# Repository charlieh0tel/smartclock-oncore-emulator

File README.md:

# smartclock-oncore-emulator

*Two VP Oncores (top left) and two boards, each on a test jig.*

A drop-in replacement for the Motorola VP Oncore GPS engine in HP and
Symmetricom SmartClocks: the Z3801A, Z3805A, 58503A and their kin.  A
u-blox LEA-M8T timing module and an STM32C091 speak the Oncore
protocol to the instrument and pass the module's 1 PPS straight
through.

It is not a full Oncore replacement.  It implements exactly the Oncore
messages that every known HP SmartClock firmware sends, each in full,
and no others (`docs/oncore-messages.md`).

## Status

- Firmware [fw-v1.0.0](https://github.com/charlieh0tel/smartclock-oncore-emulator/releases/tag/fw-v1.0.0):
  an image for each receiver model, with SHA256SUMS.
- Every SmartClock image locks in emulation, against the board on
  its test jig
  ([coverage](https://charlieh0tel.github.io/smartclock-oncore-emulator/coverage.html),
  `docs/testing.md`).
- In a 58503A, 16 hours locked with no alarm, its 1 PPS checked
  against a CNS Clock II (`docs/emu-board-bring-up.md`,
  [charts](https://claude.ai/artifact/BKLhqv7PK5DPNSiXxLh1z2)).
- Like a VP Oncore, it has a fixed bias against UTC, tens of
  nanoseconds, which each instrument can trim with
  `:DIAGnostic:TOFFset` (`docs/emu-board-bring-up.md`).
- Board rev 1.0.0.

Boards are not for sale; `hardware/` and `production/` have what is
needed to have one made.

## Layout

| Path | What |
|---|---|
| `hardware/` | KiCad designs: the board and its test jig |
| `production/` | each board's fabrication files (Gerbers, BOM, placement, source) |
| `firmware/` | the Rust firmware and its host tools (`firmware/README.md`) |
| `bench/` | bench tools: flashing, 1 PPS comparison (`bench/README.md`) |
| `docs/` | the messages, the connector, bring-up and test results |
| `PLAN.md` | the design and its reasons |
| `third_party/` | vendor documents (`third_party/NOTICE`) |

## Sources

The protocol is the VP Oncore Command Reference
(`third_party/motorola/VPCommands.pdf`), implemented by smartclock-gps.
How the SmartClock firmware uses it is in
[smartclock](https://github.com/charlieh0tel/smartclock)'s
`docs/firmware/gps.md`.

## License

- Hardware: CERN-OHL-S-2.0 (`hardware/LICENSE`).  Footprints adapted
  from KiCad's library stay CC-BY-SA-4.0; each 3D model keeps its
  source's terms (the `.3dshapes` READMEs); `hardware/ee_tooling` is
  MIT OR Apache-2.0.
- Firmware and documentation: GPL-3.0-only (`LICENSE`).
- `third_party/`: its owners' (`third_party/NOTICE`).

## Contributing

Once per clone: `git submodule update --init` and `make hooks`.
`AGENTS.md` has the rules.

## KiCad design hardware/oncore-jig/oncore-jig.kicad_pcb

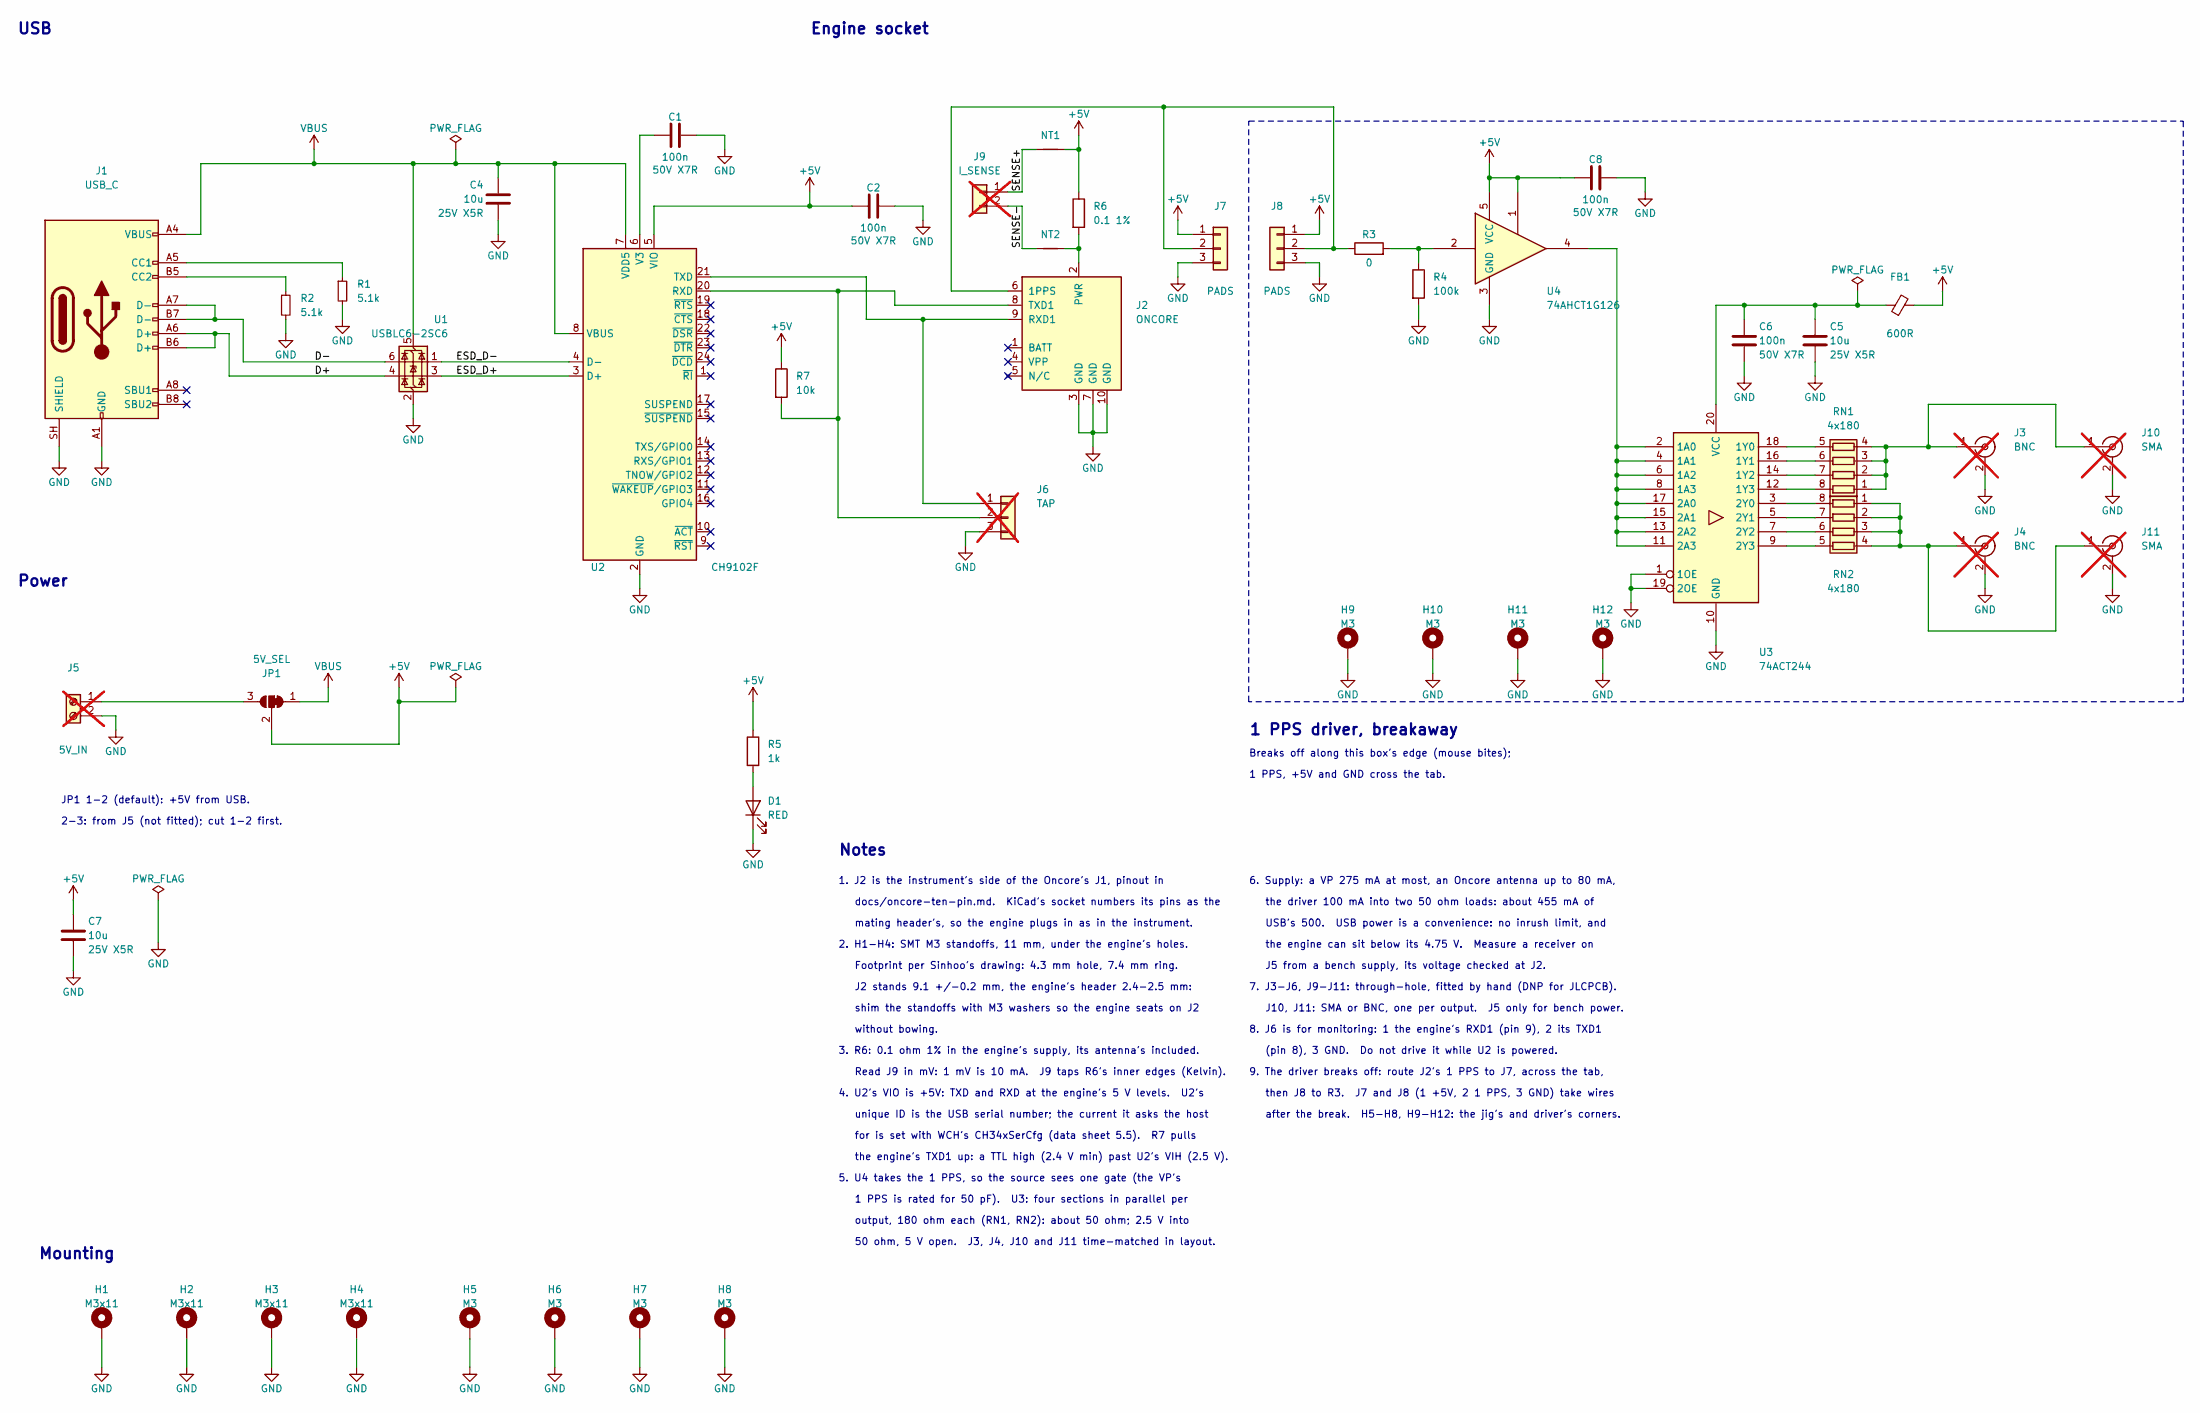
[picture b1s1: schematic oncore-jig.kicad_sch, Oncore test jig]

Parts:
C1, C2, C6, C8: 100n; C_0603_1608Metric; Rating 50V X7R; MPN CC0603KRX7R9BB104; LCSC C14663
C4, C5, C7: 10u; C_0805_2012Metric; Rating 25V X5R; MPN CL21A106KAYNNNE; LCSC C15850
D1: RED; LED_0603_1608Metric; MPN KT-0603R; LCSC C2286
FB1: 600R; L_0603_1608Metric; MPN GZ1608D601TF; LCSC C1002
H1, H2, H3, H4: M3x11; Sinhoo_SMTSO30110CTJ-B; MPN SMTSO30110CTJ-B; LCSC C2916372
H5, H6, H7, H8, H9, H10, H11, H12: M3; MountingHole_3.2mm_Pad5.0_Via
J1: USB_C; USB_C_Receptacle_HRO_TYPE-C-31-M-12; MPN TYPE-C-31-M-12; LCSC C165948
J2: ONCORE; PinSocket_2x05_P2.54mm_Vertical_SMD_BOOMELE; MPN 2.54-2*5P; LCSC C261072
J3, J4: BNC; BNC_TEConnectivity_1478035_Horizontal; MPN 1-1478035-0; not fitted
J5: 5V_IN; TerminalBlock_Phoenix_MPT-0,5-2-2.54_1x02_P2.54mm_Horizontal; MPN 1725656; not fitted
J6: TAP; PinHeader_1x03_P2.54mm_Vertical; MPN PZ254V-11-03P; LCSC C2937625; not fitted
J7, J8: PADS; PinHeader_1x03_P2.54mm_Vertical
J9: I_SENSE; PinHeader_1x02_P2.54mm_Vertical; MPN PZ254V-11-02P; LCSC C492401; not fitted
J10, J11: SMA; SMA_BAT_Wireless_BWSMA-KWE-Z001; MPN BWSMA-KWE-Z001; LCSC C496551; not fitted
JP1: 5V_SEL; SolderJumper-3_P1.3mm_Bridged12_RoundedPad1.0x1.5mm_NumberL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
NT1, NT2: NetTie_2; NetTie-2_SMD_Pad0.5mm
R1, R2: 5.1k; R_0603_1608Metric; MPN 0603WAF5101T5E; LCSC C23186
R3: 0; R_0603_1608Metric; MPN 0603WAF0000T5E; LCSC C21189
R4: 100k; R_0603_1608Metric; MPN 0603WAF1003T5E; LCSC C25803
R5: 1k; R_0603_1608Metric; MPN 0603WAF1001T5E; LCSC C21190
R6: 0.1 1%; R_0805_2012Metric; MPN FBF05FTPR100; LCSC C2929805
R7: 10k; R_0603_1608Metric; MPN 0603WAF1002T5E; LCSC C25804
RN1, RN2: 4x180; R_Array_Convex_4x0603; MPN 4D03WGJ0181T5E; LCSC C11998
U1: USBLC6-2SC6; SOT-23-6; MPN USBLC6-2SC6; LCSC C7519
U2: CH9102F; QFN-24-1EP_4x4mm_P0.5mm_EP2.6x2.6mm_CenterVia; MPN CH9102F; LCSC C2858418
U3: 74ACT244; TSSOP-20_4.4x6.5mm_P0.65mm; MPN SN74ACT244PWR; LCSC C6930
U4: 74AHCT1G126; SOT-23-5; MPN SN74AHCT1G126DBVR; LCSC C163712

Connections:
+5V: C2.1, C7.1, C8.1, FB1.2, J7.1, J8.1, JP1.2 (C), NT1.2, R5.1, R6.1, R7.1, U2.5 (VIO), U4.1, U4.5 (VCC)
/D+: J1.A6 (D+), J1.B6 (D+), U1.4 (I/O2)
/D-: J1.A7 (D-), J1.B7 (D-), U1.6 (I/O1)
/ESD_D+: U1.3 (I/O2), U2.3 (D+)
/ESD_D-: U1.1 (I/O1), U2.4 (D-)
/SENSE+: J9.1, NT1.1
/SENSE-: J9.2, NT2.1
GND: C1.2, C2.2, C4.2, C5.2, C6.2, C7.2, C8.2, D1.1 (K), H1.1, H2.1, H3.1, H4.1, H5.1, H6.1, H7.1, H8.1, H9.1, H10.1, H11.1, H12.1, J1.A1 (GND), J1.A12 (GND), J1.B1 (GND), J1.B12 (GND), J1.SH (SHIELD), J2.3 (GND), J2.7 (GND), J2.10 (GND), J3.2 (Ext), J4.2 (Ext), J5.2, J6.3, J7.3, J8.3, J10.2 (Ext), J11.2 (Ext), R1.2, R2.2, R4.2, U1.2 (GND), U2.2 (GND), U2.25 (GND), U3.1 (1OE), U3.10 (GND), U3.19 (2OE), U4.3 (GND)
unnamed: D1.2 (A), R5.2
unnamed: J1.A5 (CC1), R1.1
unnamed: J1.B5 (CC2), R2.1
unnamed: J2.6 (1PPS), J7.2, J8.2, R3.1
unnamed: J2.2 (PWR), NT2.2, R6.2
unnamed: J2.9 (RXD1), J6.1, U2.21 (TXD)
unnamed: J2.8 (TXD1), J6.2, R7.2, U2.20 (RXD)
unnamed: J5.1, JP1.3 (B)
unnamed: J3.1 (In), J10.1 (In), RN1.1 (R1.1), RN1.2 (R2.1), RN1.3 (R3.1), RN1.4 (R4.1)
unnamed: J4.1 (In), J11.1 (In), RN2.1 (R1.1), RN2.2 (R2.1), RN2.3 (R3.1), RN2.4 (R4.1)
unnamed: R3.2, R4.1, U4.2
unnamed: RN1.8 (R1.2), U3.12 (1Y3)
unnamed: RN1.7 (R2.2), U3.14 (1Y2)
unnamed: RN1.6 (R3.2), U3.16 (1Y1)
unnamed: RN1.5 (R4.2), U3.18 (1Y0)
unnamed: RN2.8 (R1.2), U3.3 (2Y0)
unnamed: RN2.7 (R2.2), U3.5 (2Y1)
unnamed: RN2.6 (R3.2), U3.7 (2Y2)
unnamed: RN2.5 (R4.2), U3.9 (2Y3)
unnamed: C1.1, U2.6 (V3)
unnamed: U3.2 (1A0), U3.4 (1A1), U3.6 (1A2), U3.8 (1A3), U3.11 (2A3), U3.13 (2A2), U3.15 (2A1), U3.17 (2A0), U4.4
unnamed: C5.1, C6.1, FB1.1, U3.20 (VCC)
VBUS: C4.1, J1.A4 (VBUS), J1.A9 (VBUS), J1.B4 (VBUS), J1.B9 (VBUS), JP1.1 (A), U1.5 (VBUS), U2.7 (VDD5), U2.8 (VBUS)

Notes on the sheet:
the driver 100 mA into two 50 ohm loads: about 455 mA of
mating header's, so the engine plugs in as in the instrument.
USB's 500. USB power is a convenience: no inrush limit, and
3. R6: 0.1 ohm 1% in the engine's supply, its antenna's included.
JP1 1-2 (default): +5V from USB.
Mounting
for is set with WCH's CH34xSerCfg (data sheet 5.5). R7 pulls
USB
Footprint per Sinhoo's drawing: 4.3 mm hole, 7.4 mm ring.
shim the standoffs with M3 washers so the engine seats on J2
1 PPS is rated for 50 pF). U3: four sections in parallel per
50 ohm, 5 V open. J3, J4, J10 and J11 time-matched in layout.
9. The driver breaks off: route J2's 1 PPS to J7, across the tab,
8. J6 is for monitoring: 1 the engine's RXD1 (pin 9), 2 its TXD1
the engine can sit below its 4.75 V. Measure a receiver on
1 PPS, +5V and GND cross the tab.
the engine's TXD1 up: a TTL high (2.4 V min) past U2's VIH (2.5 V).
then J8 to R3. J7 and J8 (1 +5V, 2 1 PPS, 3 GND) take wires
2-3: from J5 (not fitted); cut 1-2 first.
J2 stands 9.1 +/-0.2 mm, the engine's header 2.4-2.5 mm:
J10, J11: SMA or BNC, one per output. J5 only for bench power.
output, 180 ohm each (RN1, RN2): about 50 ohm; 2.5 V into
2. H1-H4: SMT M3 standoffs, 11 mm, under the engine's holes.
5. U4 takes the 1 PPS, so the source sees one gate (the VP's
unique ID is the USB serial number; the current it asks the host
(pin 8), 3 GND. Do not drive it while U2 is powered.
Power
docs/oncore-ten-pin.md. KiCad's socket numbers its pins as the
J5 from a bench supply, its voltage checked at J2.
after the break. H5-H8, H9-H12: the jig's and driver's corners.
Engine socket
Read J9 in mV: 1 mV is 10 mA. J9 taps R6's inner edges (Kelvin).
Notes
1. J2 is the instrument's side of the Oncore's J1, pinout in
Breaks off along this box's edge (mouse bites);
7. J3-J6, J9-J11: through-hole, fitted by hand (DNP for JLCPCB).
1 PPS driver, breakaway
without bowing.
4. U2's VIO is +5V: TXD and RXD at the engine's 5 V levels. U2's
6. Supply: a VP 275 mA at most, an Oncore antenna up to 80 mA,

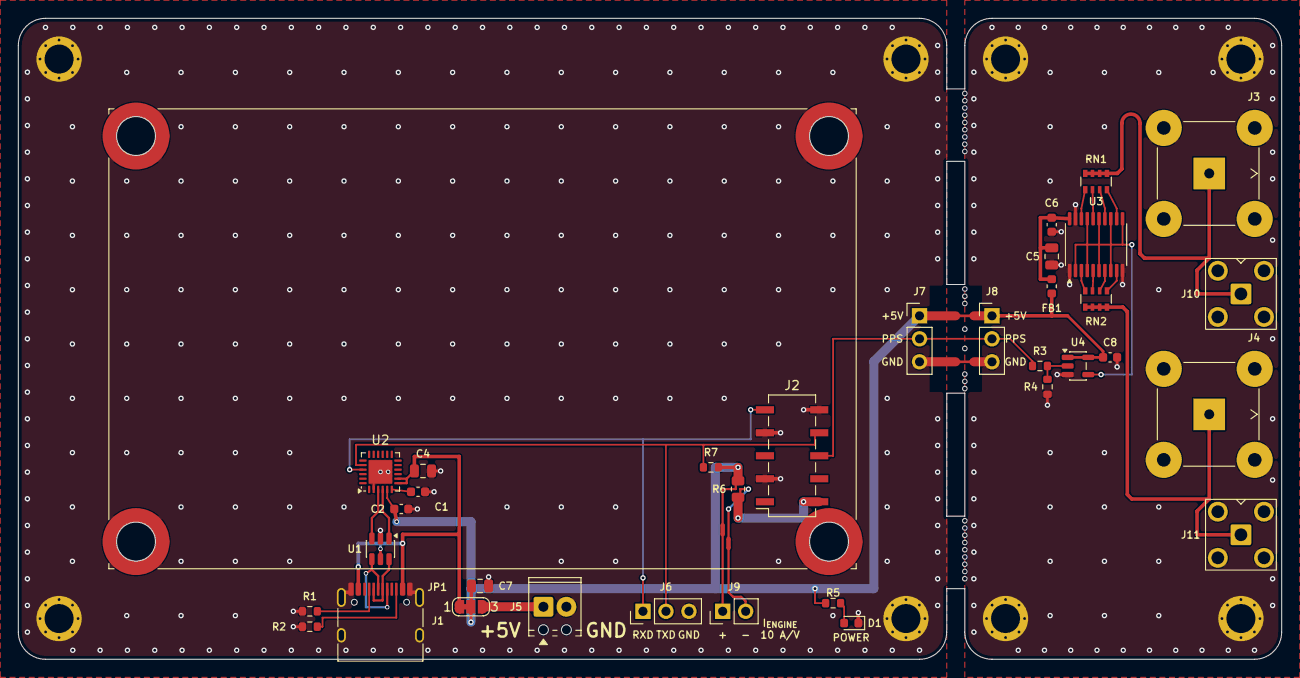
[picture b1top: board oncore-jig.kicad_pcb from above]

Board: 2 copper layers, 139.6 x 70.8 mm, 51 parts (0 on the bottom side), 31 nets.

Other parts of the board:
MB1, MB2, MB3: MouseBites

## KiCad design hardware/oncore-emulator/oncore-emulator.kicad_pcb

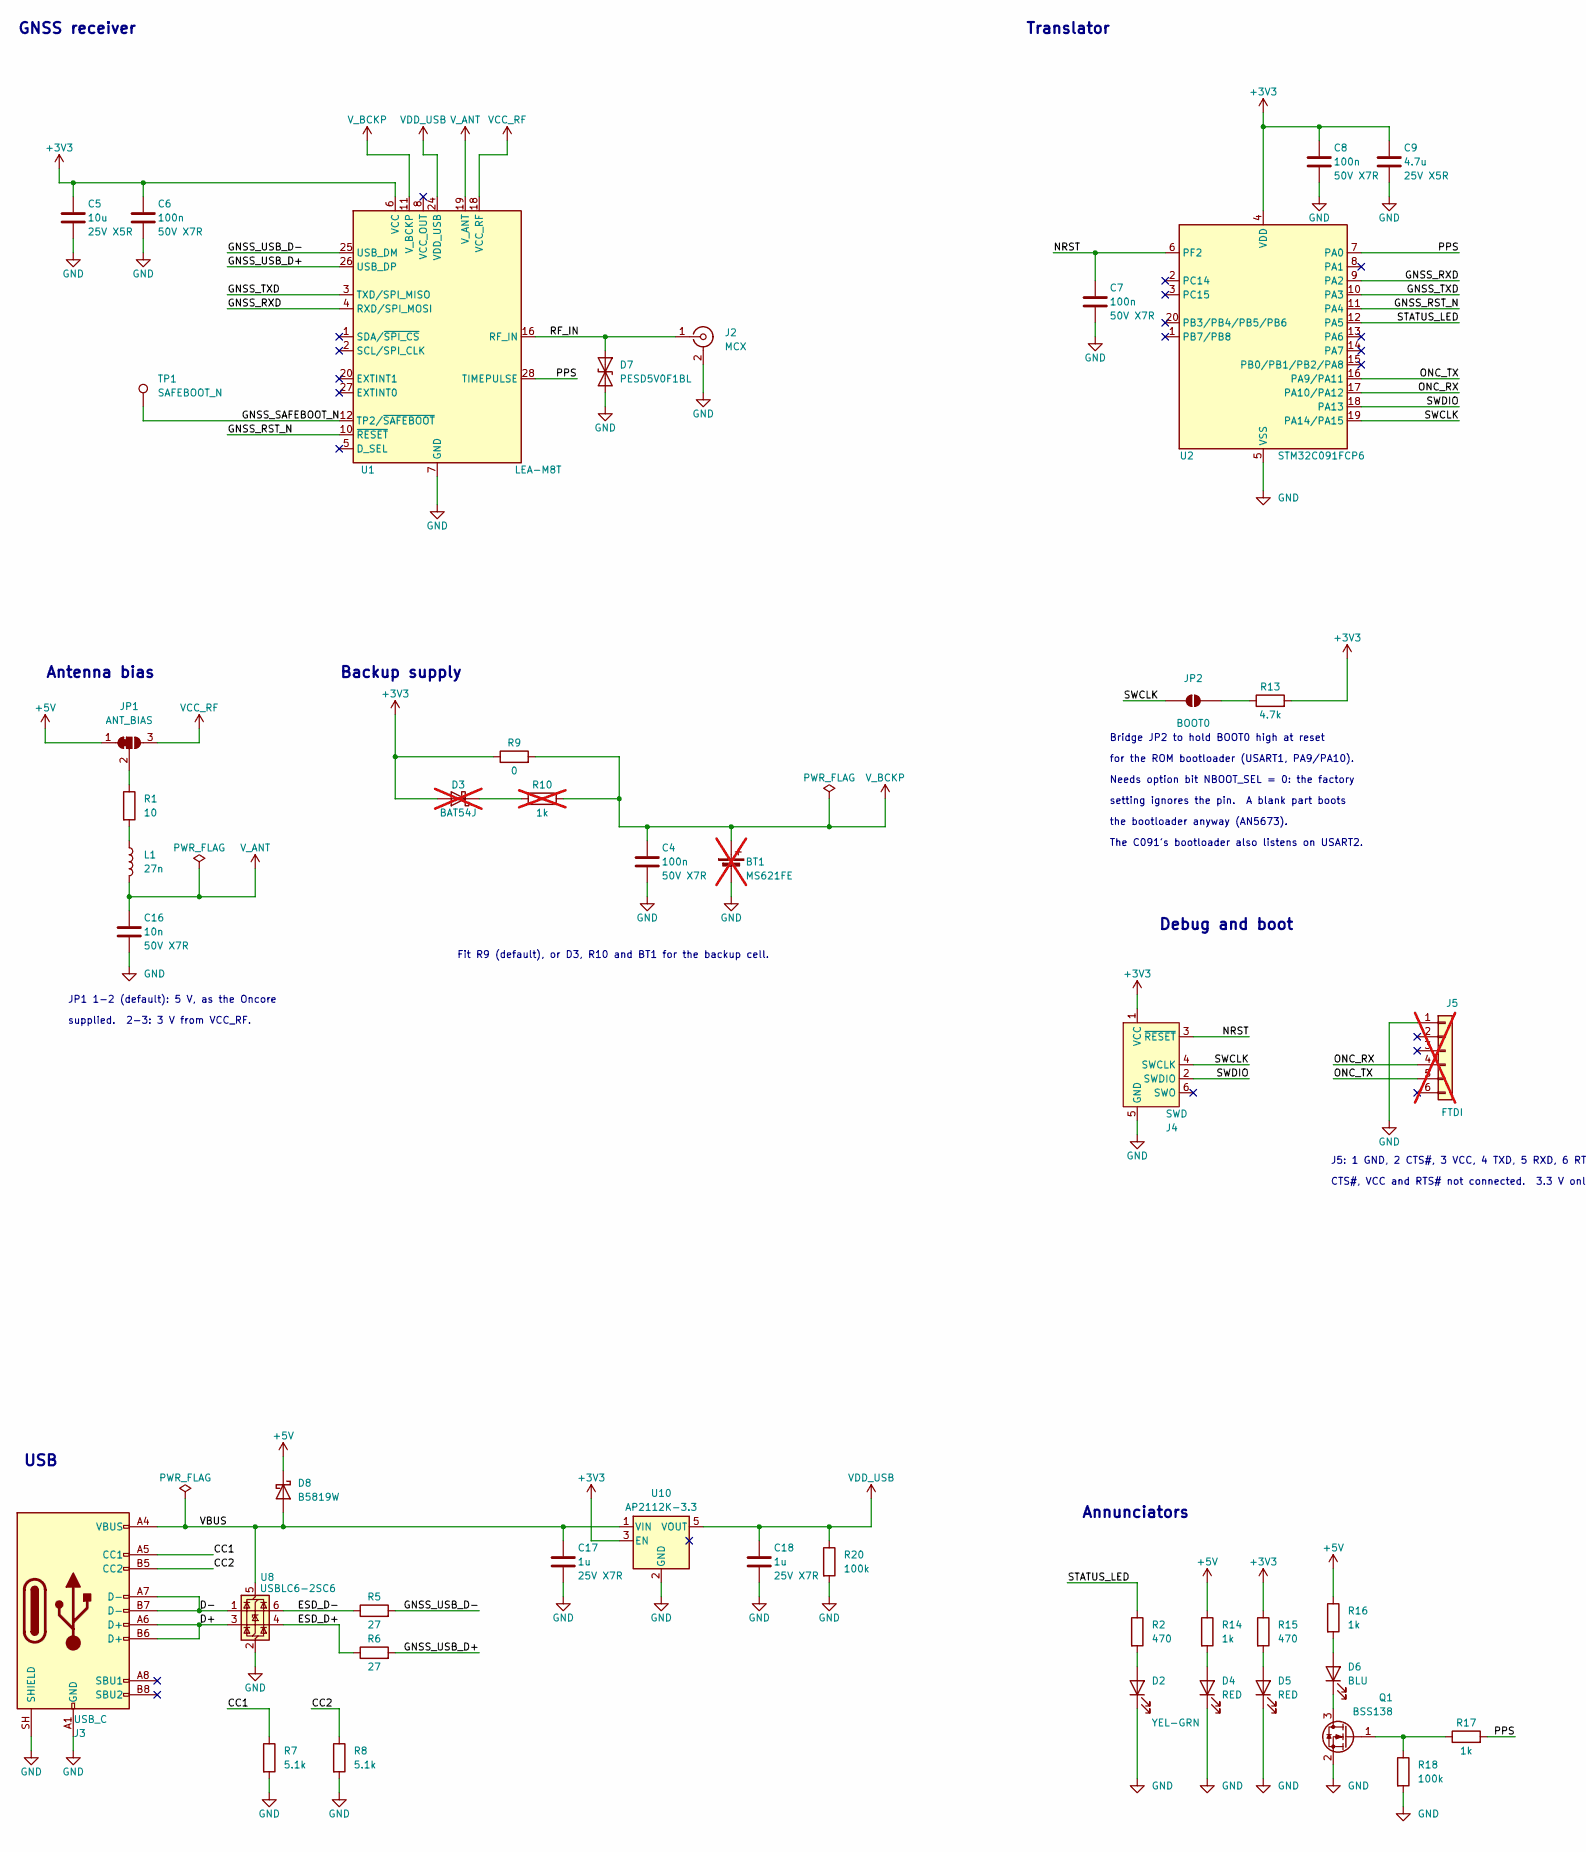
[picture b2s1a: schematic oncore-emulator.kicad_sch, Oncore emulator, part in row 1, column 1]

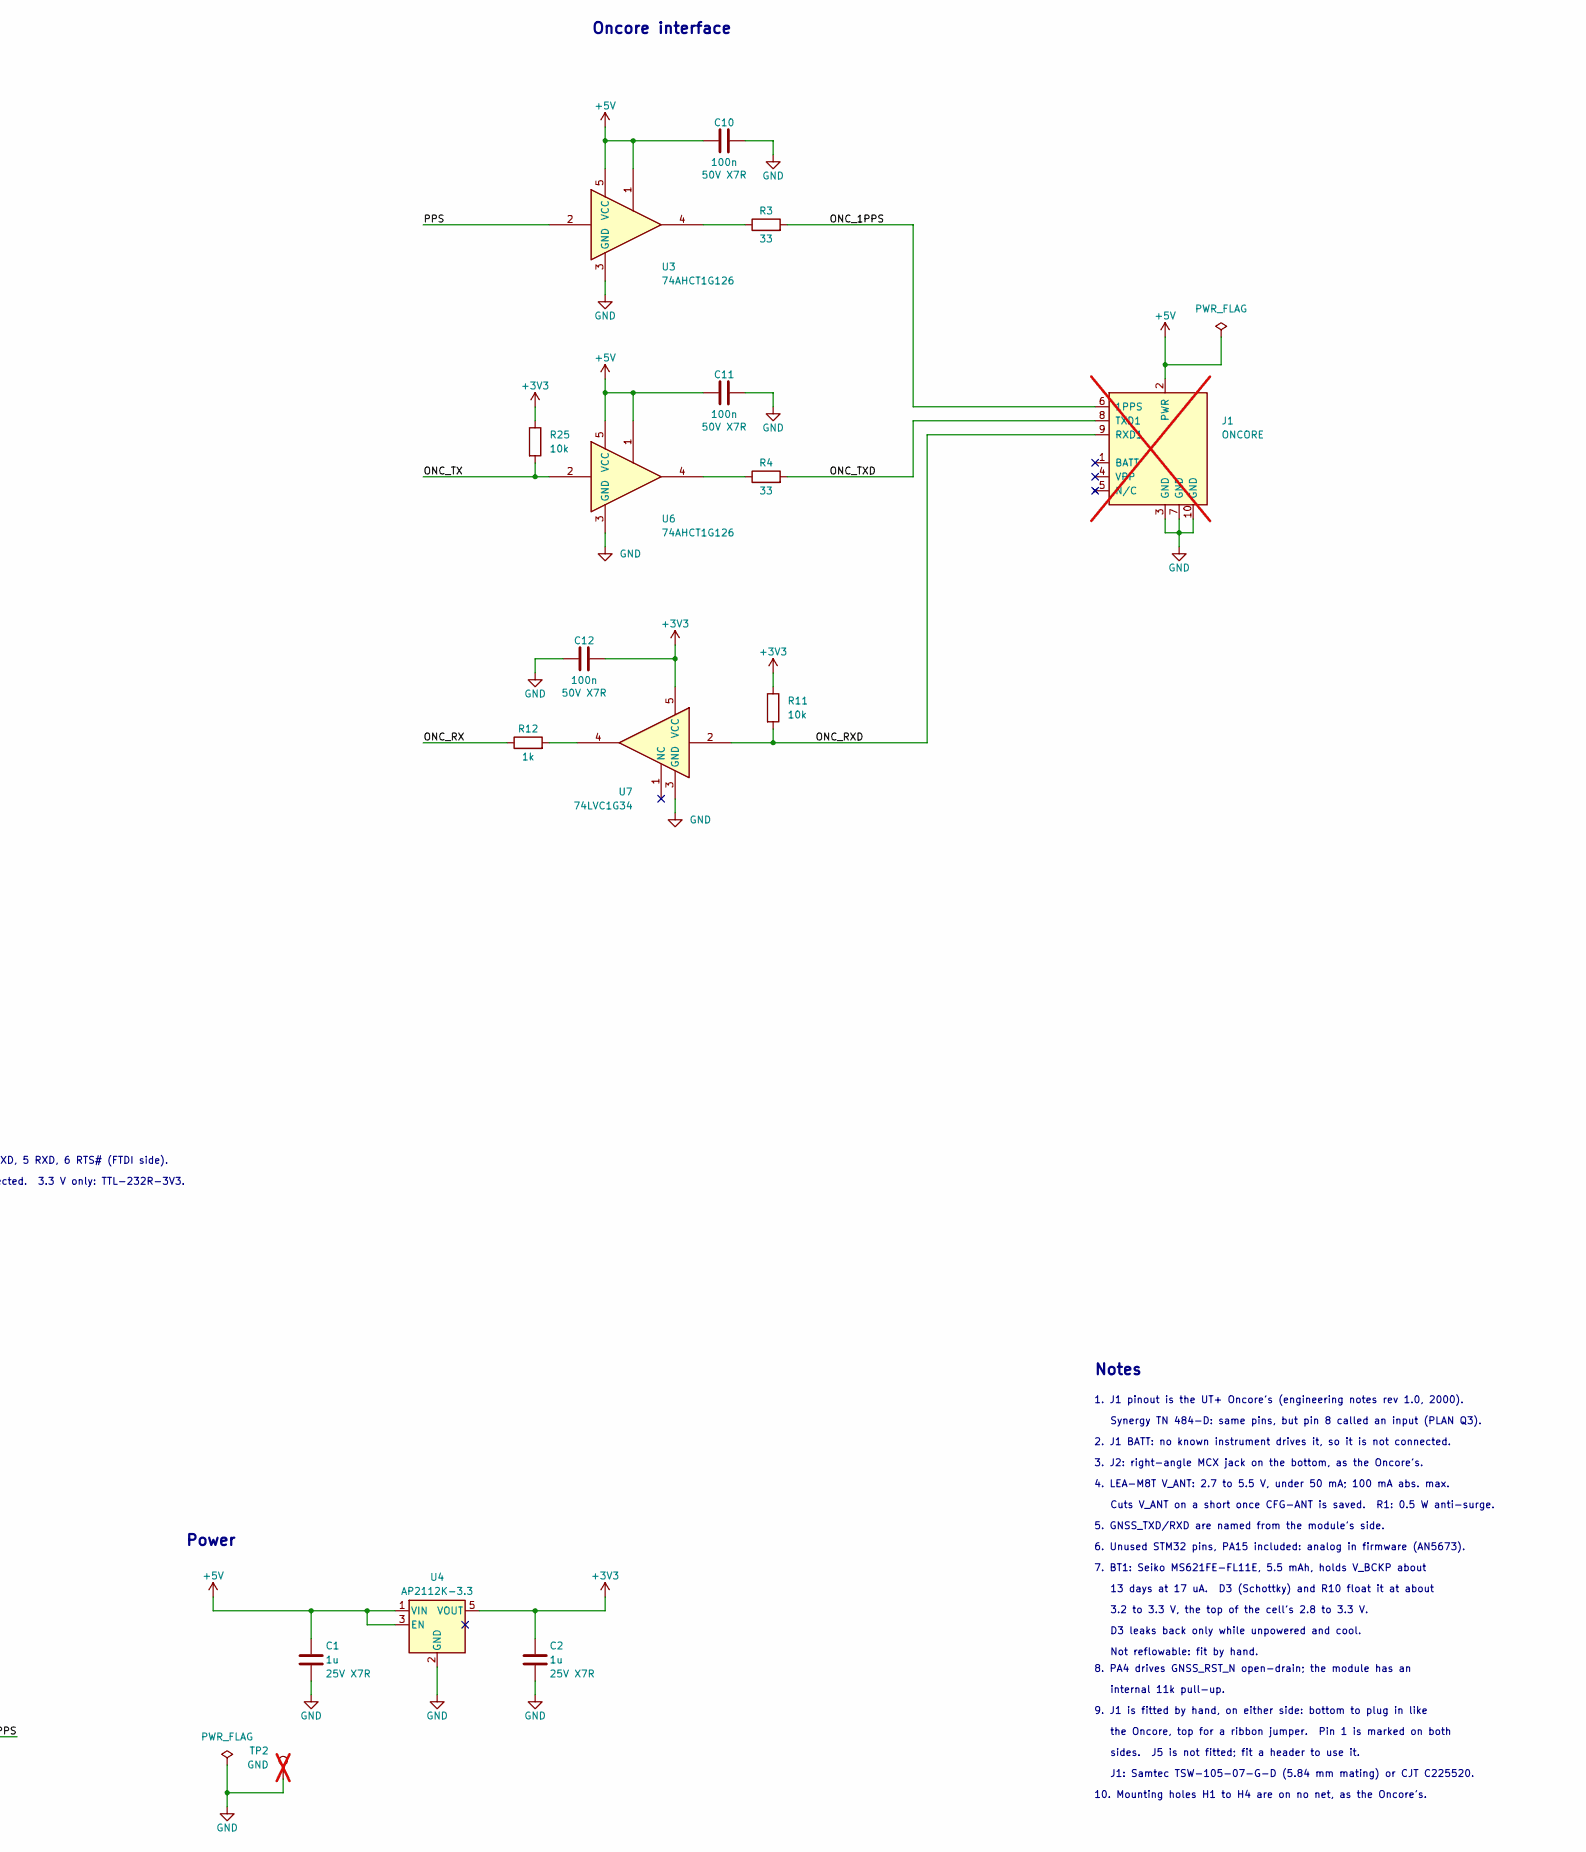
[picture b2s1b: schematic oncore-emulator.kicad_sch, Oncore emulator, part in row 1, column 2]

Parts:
BT1: MS621FE; BatteryHolder_Seiko_MS621F; MPN MS621FE-FL11E; not fitted
C1, C2, C17, C18: 1u; C_0603_1608Metric; Rating 25V X7R; MPN CL10B105KA8NNNC; LCSC C29936
C4, C6, C7, C8, C10, C11, C12: 100n; C_0603_1608Metric; Rating 50V X7R; MPN CC0603KRX7R9BB104; LCSC C14663
C5: 10u; C_0805_2012Metric; Rating 25V X5R; MPN CL21A106KAYNNNE; LCSC C15850
C9: 4.7u; C_0805_2012Metric; Rating 25V X5R; MPN CL21A475KAQNNNE; LCSC C1779
C16: 10n; C_0603_1608Metric; Rating 50V X7R; MPN 0603B103K500NT; LCSC C57112
D2: YEL-GRN; LED_0603_1608Metric; MPN KT-0603YG; LCSC C2289
D3: BAT54J; D_SOD-323F; MPN BAT54J,115; LCSC C130415; not fitted
D4, D5: RED; LED_0603_1608Metric; MPN KT-0603R; LCSC C2286
D6: BLU; LED_0603_1608Metric; MPN KT-0603B; LCSC C2288
D7: PESD5V0F1BL; D_SOD-882; MPN PESD5V0F1BL,315; LCSC C45961
D8: B5819W; D_SOD-123; MPN B5819W SL; LCSC C8598
J1: ONCORE; PinHeader_2x05_P2.54mm_Vertical; MPN TSW-105-07-G-D; not fitted
J2: MCX; MCX_Jack_Horizontal_THT_5.08mm; MPN BWMCX-KWE; LCSC C5137196
J3: USB_C; USB_C_Receptacle_HRO_TYPE-C-31-M-12; MPN TYPE-C-31-M-12; LCSC C165948
J4: SWD; Tag-Connect_TC2030-IDC-NL_2x03_P1.27mm_Vertical
J5: FTDI; PinHeader_1x06_P2.54mm_Horizontal; MPN HX PZ2.54-1x6P WZ; LCSC C32713265; not fitted
JP1: ANT_BIAS; SolderJumper-3_P1.3mm_Bridged12_RoundedPad1.0x1.5mm
JP2: BOOT0; SolderJumper-2_P1.3mm_Open_RoundedPad1.0x1.5mm
L1: 27n; L_0603_1608Metric; MPN LQW18AN27NG80D; LCSC C6080189
Q1: BSS138; SOT-23; MPN BSS138LT1G; LCSC C82045
R1: 10; R_0805_2012Metric; MPN ERJ-P06F10R0V; LCSC C441969
R2, R15: 470; R_0603_1608Metric; MPN 0603WAF4700T5E; LCSC C23179
R3, R4: 33; R_0603_1608Metric; MPN 0603WAF330JT5E; LCSC C23140
R5, R6: 27; R_0603_1608Metric; MPN 0603WAF270JT5E; LCSC C25190
R7, R8: 5.1k; R_0603_1608Metric; MPN 0603WAF5101T5E; LCSC C23186
R9: 0; R_0603_1608Metric; MPN 0603WAF0000T5E; LCSC C21189
R10: 1k; R_0603_1608Metric; MPN 0603WAF1001T5E; LCSC C21190; not fitted
R11, R25: 10k; R_0603_1608Metric; MPN 0603WAF1002T5E; LCSC C25804
R12, R14, R16, R17: 1k; R_0603_1608Metric; MPN 0603WAF1001T5E; LCSC C21190
R13: 4.7k; R_0603_1608Metric; MPN 0603WAF4701T5E; LCSC C23162
R18, R20: 100k; R_0603_1608Metric; MPN 0603WAF1003T5E; LCSC C25803
TP1: SAFEBOOT_N; TestPoint_Pad_D1.0mm
TP2: GND; TestPoint_Keystone_5019_Miniature; MPN 5019; LCSC C238131; not fitted
U1: LEA-M8T; ublox_LEA; MPN LEA-M8T-0; LCSC C2763452
U2: STM32C091FCP6; TSSOP-20_4.4x6.5mm_P0.65mm; MPN STM32C091FCP6; LCSC C45338507
U3, U6: 74AHCT1G126; SOT-23-5; MPN SN74AHCT1G126DBVR; LCSC C163712
U4, U10: AP2112K-3.3; SOT-23-5; MPN AP2112K-3.3TRG1; LCSC C51118
U7: 74LVC1G34; SOT-23-5; MPN SN74LVC1G34DBVR; LCSC C840096
U8: USBLC6-2SC6; SOT-23-6; MPN USBLC6-2SC6; LCSC C7519

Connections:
+3V3: C2.1, C5.1, C6.1, C8.1, C9.1, C12.1, D3.2 (A), J4.1 (VCC), R9.1, R11.1, R13.2, R15.1, R25.1, U1.6 (VCC), U2.4 (VDD), U4.5 (VOUT), U7.5 (VCC), U10.3 (EN)
+5V: C1.1, C10.1, C11.1, D8.1 (K), J1.2 (PWR), JP1.1 (A), R14.1, R16.1, U3.1, U3.5 (VCC), U4.1 (VIN), U4.3 (EN), U6.1, U6.5 (VCC)
/CC1: J3.A5 (CC1), R7.1
/CC2: J3.B5 (CC2), R8.1
/D+: J3.A6 (D+), J3.B6 (D+), U8.3 (I/O2)
/D-: J3.A7 (D-), J3.B7 (D-), U8.1 (I/O1)
/ESD_D+: R6.1, U8.4 (I/O2)
/ESD_D-: R5.1, U8.6 (I/O1)
/GNSS_RST_N: U1.10 (~RESET), U2.11 (PA4)
/GNSS_RXD: U1.4 (RXD/SPI_MOSI), U2.9 (PA2)
/GNSS_SAFEBOOT_N: TP1.1 (1_1), U1.12 (TP2/~SAFEBOOT)
/GNSS_TXD: U1.3 (TXD/SPI_MISO), U2.10 (PA3)
/GNSS_USB_D+: R6.2, U1.26 (USB_DP)
/GNSS_USB_D-: R5.2, U1.25 (USB_DM)
/NRST: C7.1, J4.3 (~RESET), U2.6 (PF2)
/ONC_1PPS: J1.6 (1PPS), R3.2
/ONC_RX: J5.4, R12.1, U2.17 (PA10/PA12)
/ONC_RXD: J1.9 (RXD1), R11.2, U7.2
/ONC_TX: J5.5, R25.2, U2.16 (PA9/PA11), U6.2
/ONC_TXD: J1.8 (TXD1), R4.2
/PPS: R17.2, U1.28 (TIMEPULSE), U2.7 (PA0), U3.2
/RF_IN: D7.1 (A1), J2.1 (In), U1.16 (RF_IN)
/STATUS_LED: R2.1, U2.12 (PA5)
/SWCLK: J4.4 (SWCLK), JP2.1 (A), U2.19 (PA14)
/SWDIO: J4.2 (SWDIO), U2.18 (PA13)
/VBUS: C17.1, D8.2 (A), J3.A4 (VBUS), J3.A9 (VBUS), J3.B4 (VBUS), J3.B9 (VBUS), U8.5 (VBUS), U10.1 (VIN)
GND: BT1.2 (-), C1.2, C2.2, C4.2, C5.2, C6.2, C7.2, C8.2, C9.2, C10.2, C11.2, C12.2, C16.2, C17.2, C18.2, D2.1 (K), D4.1 (K), D5.1 (K), D7.2 (A2), J1.3 (GND), J1.7 (GND), J1.10 (GND), J2.2 (Ext), J3.A1 (GND), J3.A12 (GND), J3.B1 (GND), J3.B12 (GND), J3.SH (SHIELD), J4.5 (GND), J5.1, Q1.2 (S), R7.2, R8.2, R18.2, R20.2, TP2.1 (1_1), U1.7 (GND), U1.13 (GND), U1.14 (GND), U1.15 (GND), U1.17 (GND), U2.5 (VSS), U3.3 (GND), U4.2 (GND), U6.3 (GND), U7.3 (GND), U8.2 (GND), U10.2 (GND)
unnamed: D2.2 (A), R2.2
unnamed: D3.1 (K), R10.1
unnamed: D4.2 (A), R14.2
unnamed: D5.2 (A), R15.2
unnamed: D6.2 (A), R16.2
unnamed: D6.1 (K), Q1.3 (D)
unnamed: JP1.2 (C), R1.1
unnamed: JP2.2 (B), R13.1
unnamed: L1.1, R1.2
unnamed: Q1.1 (G), R17.1, R18.1
unnamed: R3.1, U3.4
unnamed: R4.1, U6.4
unnamed: R12.2, U7.4
VCC_RF: JP1.3 (B), U1.18 (VCC_RF)
VDD_USB: C18.1, R20.1, U1.24 (VDD_USB), U10.5 (VOUT)
V_ANT: C16.1, L1.2, U1.19 (V_ANT)
V_BCKP: BT1.1 (+), C4.1, R9.2, R10.2, U1.11 (V_BCKP)

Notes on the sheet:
sides. J5 is not fitted; fit a header to use it.
J1: Samtec TSW-105-07-G-D (5.84 mm mating) or CJT C225520.
for the ROM bootloader (USART1, PA9/PA10).
J5: 1 GND, 2 CTS#, 3 VCC, 4 TXD, 5 RXD, 6 RTS# (FTDI side).
4. LEA-M8T V_ANT: 2.7 to 5.5 V, under 50 mA; 100 mA abs. max.
Annunciators
the Oncore, top for a ribbon jumper. Pin 1 is marked on both
USB
3. J2: right-angle MCX jack on the bottom, as the Oncore's.
7. BT1: Seiko MS621FE-FL11E, 5.5 mAh, holds V_BCKP about
Cuts V_ANT on a short once CFG-ANT is saved. R1: 0.5 W anti-surge.
the bootloader anyway (AN5673).
The C091's bootloader also listens on USART2.
8. PA4 drives GNSS_RST_N open-drain; the module has an
Oncore interface
Notes
JP1 1-2 (default): 5 V, as the Oncore
Antenna bias
Synergy TN 484-D: same pins, but pin 8 called an input (PLAN Q3).
CTS#, VCC and RTS# not connected. 3.3 V only: TTL-232R-3V3.
Debug and boot
Fit R9 (default), or D3, R10 and BT1 for the backup cell.
6. Unused STM32 pins, PA15 included: analog in firmware (AN5673).
Backup supply
3.2 to 3.3 V, the top of the cell's 2.8 to 3.3 V.
GNSS receiver
9. J1 is fitted by hand, on either side: bottom to plug in like
10. Mounting holes H1 to H4 are on no net, as the Oncore's.
Power
setting ignores the pin. A blank part boots
internal 11k pull-up.
1. J1 pinout is the UT+ Oncore's (engineering notes rev 1.0, 2000).
supplied. 2-3: 3 V from VCC_RF.
13 days at 17 uA. D3 (Schottky) and R10 float it at about
2. J1 BATT: no known instrument drives it, so it is not connected.
D3 leaks back only while unpowered and cool.
Bridge JP2 to hold BOOT0 high at reset
Translator
Not reflowable: fit by hand.
Needs option bit NBOOT_SEL = 0: the factory

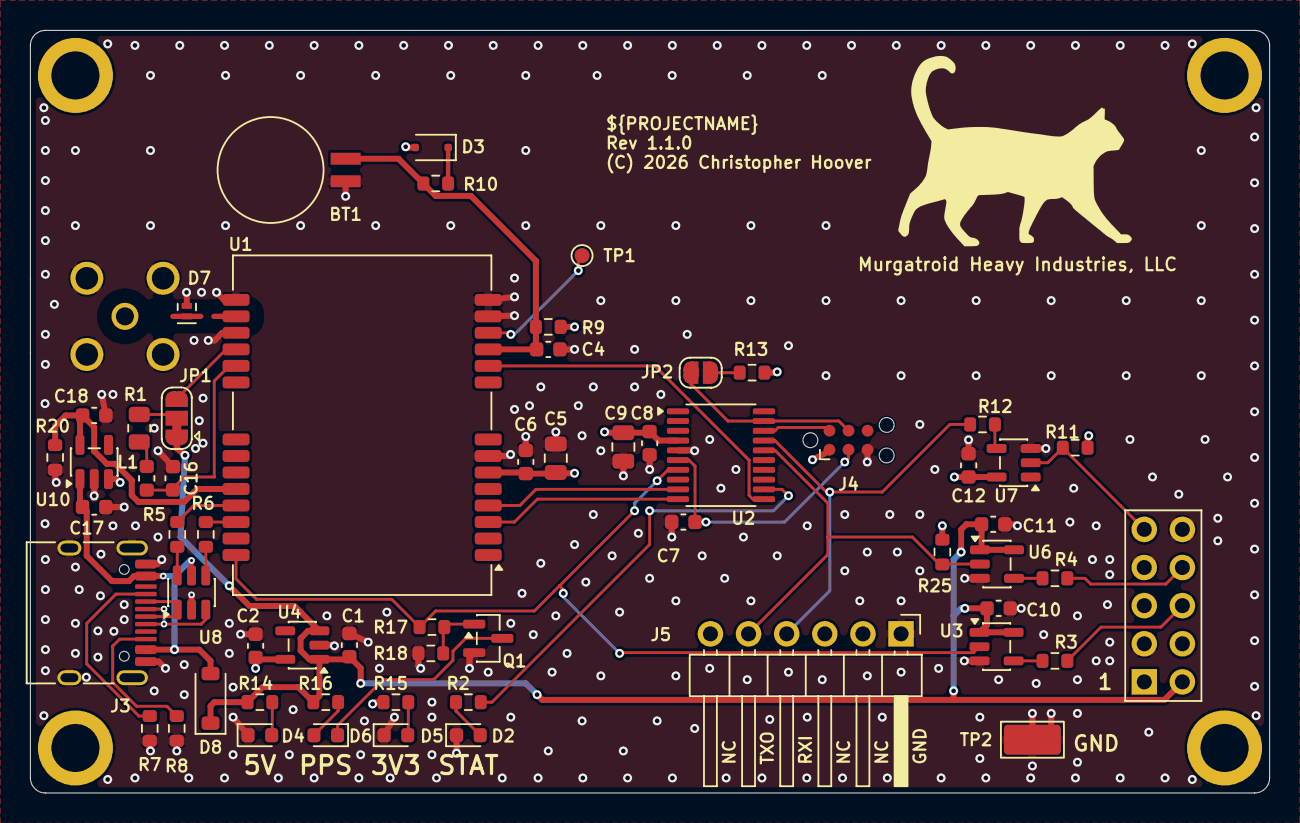
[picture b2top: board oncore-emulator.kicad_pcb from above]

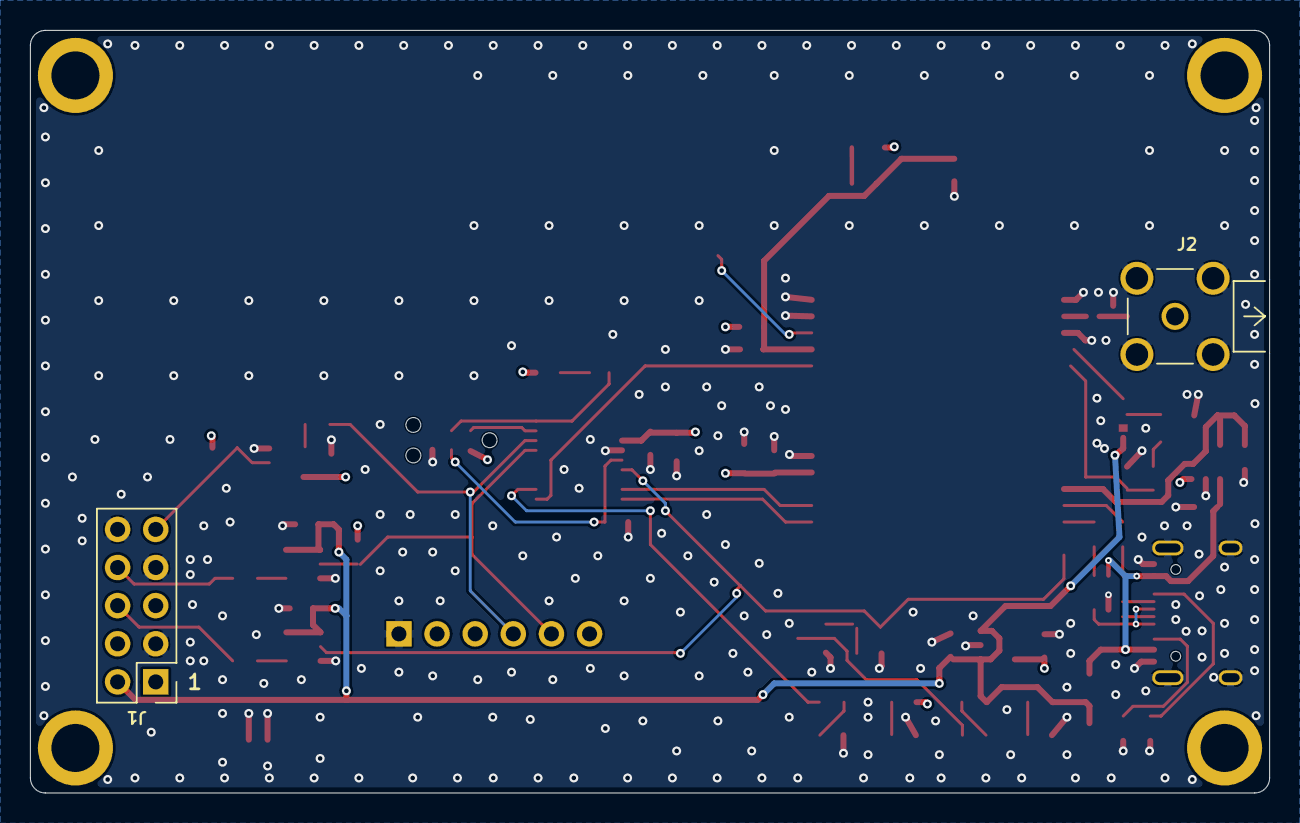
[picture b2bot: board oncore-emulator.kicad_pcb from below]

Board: 4 copper layers, 82.6 x 50.8 mm, 65 parts (2 on the bottom side), 44 nets.

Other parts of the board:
H1, H2, H3, H4: MountingHole; MountingHole_3.2mm_Pad5.0

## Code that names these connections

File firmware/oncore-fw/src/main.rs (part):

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const GNSS_TX: usize = 256;
/// The instrument's link: an answer as long as `@@Cj`, 294 bytes, and
/// the continuous outputs of a second, written without waiting.
const ONC_RX: usize = 256;
const ONC_TX: usize = 1024;

/// How often a write that found too little room in the transmit buffer
/// is tried again.  embassy-stm32 0.6.0's `BufferedUartTx::write` then
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    let mut watchdog = IndependentWatchdog::new(p.IWDG, WATCHDOG_TIMEOUT_US);
    watchdog.unleash();

    let gnss_reset = OutputOpenDrain::new(p.PA4, Level::High, Speed::Low);

    // Each UART at its peer's rate out of reset, 8N1.
    let (mut gnss_config, mut onc_config) = (Config::default(), Config::default());
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    onc_config.baudrate = ONCORE_BAUD.get();

    let gnss =
        BufferedUart::new(p.USART2, p.PA3, p.PA2, buffer!(GNSS_TX), buffer!(GNSS_RX), Irqs, gnss_config)
            .unwrap();
    let onc = BufferedUart::new(p.USART1, p.PA10, p.PA9, buffer!(ONC_TX), buffer!(ONC_RX), Irqs, onc_config)
        .unwrap();

    let pps = ExtiInput::new(p.PA0, p.EXTI0, Pull::None, Irqs);
    let led = Output::new(p.PA5, Level::Low, Speed::Low);

    spawner.spawn(pps_led(pps, led).unwrap());
    spawner.spawn(
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    pac::DBGMCU.apb1fzr().modify(|w| w.set_iwdg(true));
}

/// USART1's PA9 and PA10 on TSSOP20 pins 16 and 17, the instrument's,
/// which are PA11 and PA12 unless remapped (RM0490, `SYSCFG_CFGR1`); with
/// SYSCFG's clock on.  Not on the NUCLEO-C092RC, whose LQFP64 has PA9
/// and PA10 pins of their own, which the remap would turn analog, and
/// whose PA11 and PA12 go to its USB-C connector.
fn usart1_on_instrument_pins() {
    pac::RCC.apbenr2().modify(|w| w.set_syscfgen(true));
    #[cfg(not(feature = "nucleo"))]
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

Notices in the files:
hardware/oncore-emulator/oncore-emulator.kicad_pcb:
(C) 2026 Christopher Hoover
